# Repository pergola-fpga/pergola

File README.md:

# Pergola FPGA

The Pergola FPGA board is a low-cost, open-source FPGA development board featuring the Lattice ECP5 FPGA.

# Current status

## RevA 0.1

A handful of units have been built for initial test and bringup populated with LFE5U-12F-8BG256C.

It has been tested and works if the fixes below are applied.

### Errata:

- iMX ROM bootloader freezes because the UART RX pin is pulled
   low by the FPGA during boot. (FPGA pin is PL35B_VREF_1_6)
   A 4K7 pull-up is probably not enough, the voltage drops to 2.9V.
   Workaround: Bodge a 1K pull-up between UART_RX and 3V3.
- Wrong load caps for the xtal. Should be 20pF.
- SWD IO and CLK are swapped on the silk.
- IMX_BOOT_MODE_0 and IMX_BOOT_MODE_1 are swapped on the silk.
- A 1K pull-down is on the `~FPGA_HOLD~` net to allow the iMX to use the flash exclusively during boot-up.

# Firmware
TODO.

Currently I have a very ugly test project that can be loaded into the iMX's RAM using the ROM bootloader. This will open up a CDC interface that can be used to send a bitstream to the FPGA.

Currently working on porting the UF2 bootloader in order to update the firmware easily using USB and not having to use the SWD pins.

Current *horrible* hack is located over at [git.xil.se](https://git.xil.se/kbeckmann/pergola_fw) and contains a prebuilt binary.

The firmware will expose a cdc_acm device over USB. To program a bitstream, you simply have to write the number of bytes it is, followed by a newline (`\n`), followed by the bitstream.

# Getting started

- Clone my fork of the imx usb loader project:
```
git clone https://github.com/kbeckmann/imx_usb_loader && cd imx_usb_loader
```
- Checkout the `imxrt1010` branch:
```
git checkout imxrt1010
```
- Build it:
```
make
```
- Clone this repository and change to the firmware directory: (firmware is built from https://git.xil.se/kbeckmann/pergola_fw)
```
cd .. && git clone https://github.com/pergola-fpga/pergola && cd pergola/firmware
```
- Run the loader:
```
../../imx_usb_loader/imx_usb
```
. You might have to run it with `sudo`.
- Check `dmesg` to see if you got a cdc_acm device, e.g. `ttyACM0`
- Now you'll be able to send a bitstream to the board:
```
export ACM_DEVICE=/dev/ttyACM0
export PROGRAM_BIN=path/to/your/top.bin

# If you don't have setup udev rules
sudo chown $UID:$GID $ACM_DEVICE

# Configure the ACM device to be raw, this prevents weird stuff from happening when we send raw binary data.
stty -F $ACM_DEVICE 300 raw -clocal -echo icrnl;
sleep 0.01;
cat $ACM_DEVICE &;
echo -n "$(stat -c%s $PROGRAM_BIN)\n" > $ACM_DEVICE;
cp $PROGRAM_BIN $ACM_DEVICE; sync
```

- This should generate the following output more or less:
```
Reading 582369 bytes
READ_ID: ff ff ff ff 21 11 10 43

Done programming. FPGA_DONE=1
P E R G O L A

<bytes to load><\n>; Load bitstream to FPGA SRAM
```

- There is also an nmigen board definition in gateware/nmigen_wip/pergola.py

# How to contribute

Feel free to submit a PR, create an issue.

Discussion happens on [Gitter](https://gitter.im/pergola-fpga/Lobby) for the time being. You can also ping [@kbeckmann](https://twitter.com/kbeckmann) on Twitter.

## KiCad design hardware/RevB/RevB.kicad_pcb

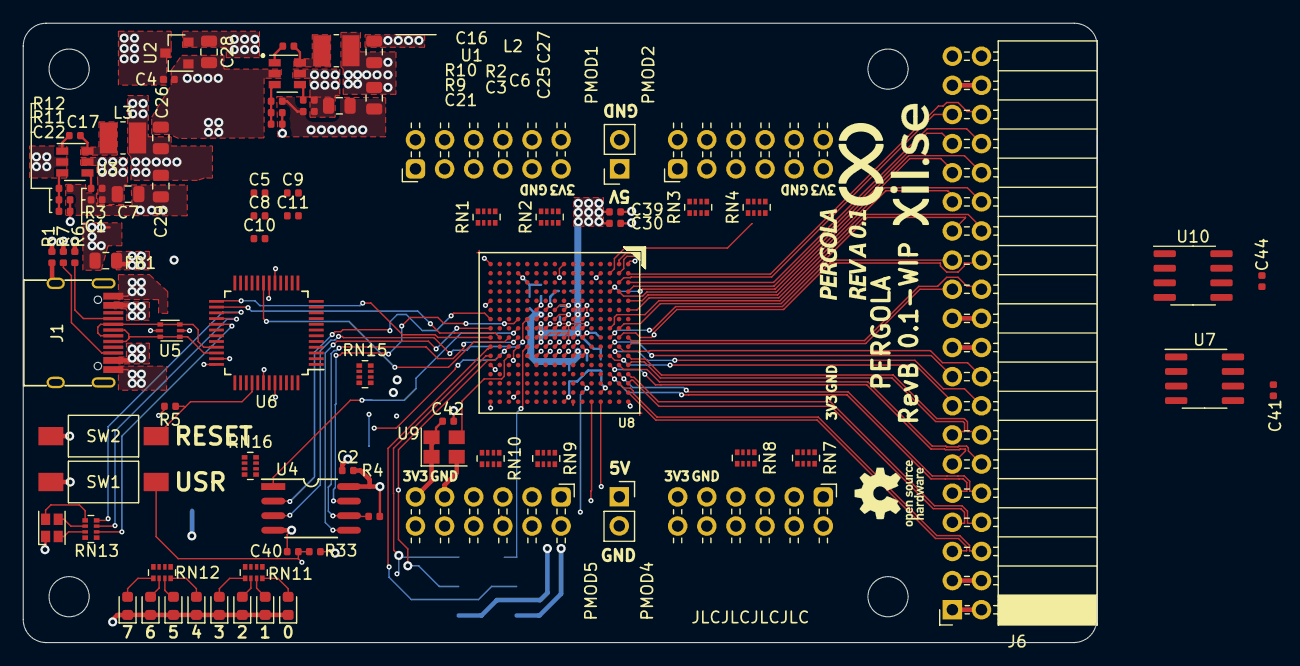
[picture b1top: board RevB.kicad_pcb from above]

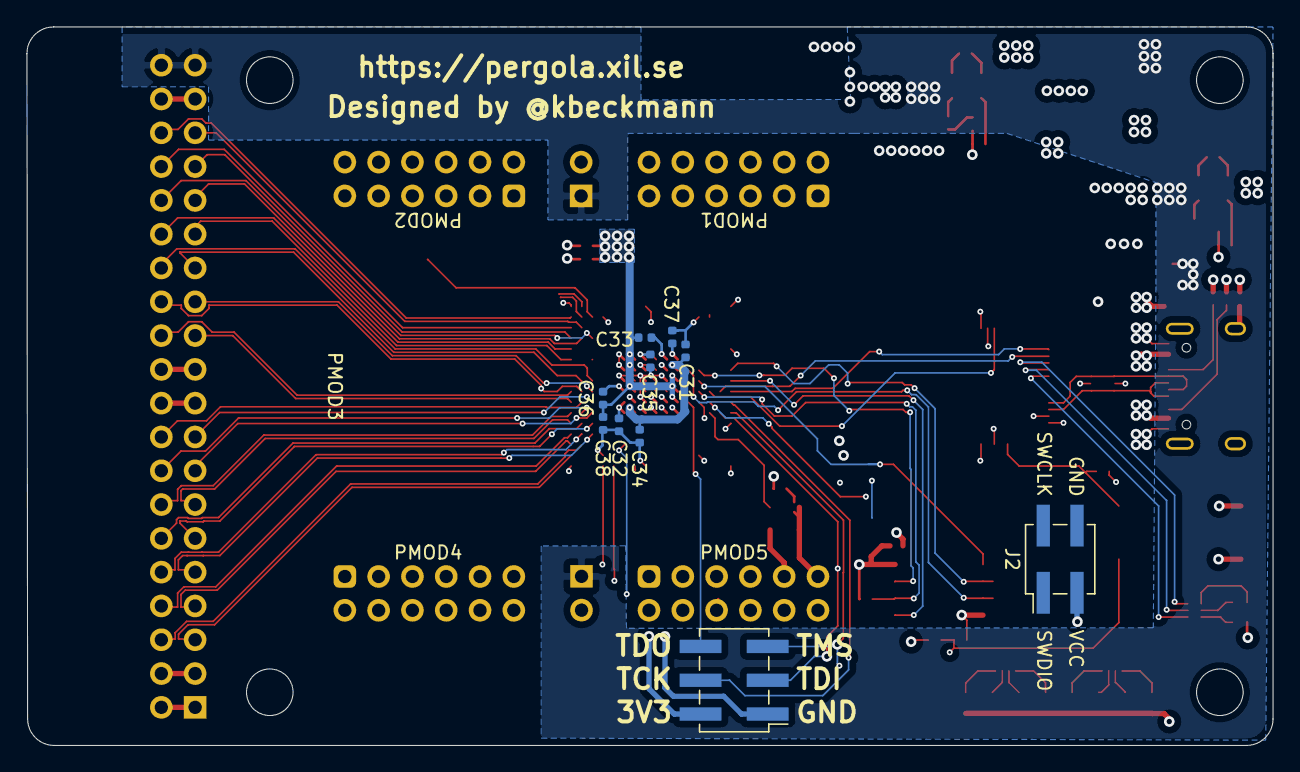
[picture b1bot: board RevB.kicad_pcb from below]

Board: 4 copper layers, 93.7 x 54.0 mm, 100 parts (10 on the bottom side), 147 nets.

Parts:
C1, C2, C3, C5, C8, C9, C10, C11, C16, C17, C30, C31, C32, C33, C34, C35, C36, C37, C38, C39, C40, C41, C42, C44: 100n; C_0402_1005Metric
C4: 4u7; C_0402_1005Metric
C6, C7, C25, C26, C27, C28, C29: 22u; C_0805_2012Metric
C21, C22: 22p; C_0402_1005Metric
D1: LED_ARGB; LED_Cree-PLCC4_2x2mm_CW
D2, D3, D4, D5, D6, D7, D8, D9: LED; LED_0603_1608Metric
FB1: Ferrite_Bead; L_0805_2012Metric
H1, H2, H3, H4: DNP; MountingHole_3.5mm
J1: USB_C_Receptacle_USB2.0; USB_C_Receptacle_GT-USB-7010
J2: DNP Conn_02x02_Odd_Even; PinHeader_2x02_P2.54mm_Vertical_SMD
J3, J5: DNP Conn_01x02; PinSocket_1x02_P2.54mm_Vertical
J4: DNP Conn_02x03_Odd_Even; PinHeader_2x03_P2.54mm_Vertical_SMD
J6: Conn_ULX3S; PinSocket_2x20_P2.54mm_Horizontal
L2, L3: 4u7 1A; L_1008_1210
LOGO1: Logo_Open_Hardware_Small; OSHW-Logo_5.7x6mm_SilkScreen
LOGO2: Logo_Open_Hardware_Small; logo
LOGO3: Logo_Open_Hardware_Small; xil_logo_new
PMOD1, PMOD2, PMOD4, PMOD5: Conn_02x06_Top_Bottom; PMOD_Socket_2x06_P2.54mm_Horizontal
R1: 100k; R_0402_1005Metric
R2, R3, R5, R33: 10k; R_0402_1005Metric
R4: 1k; R_0402_1005Metric
R6, R7: 5k1; R_0402_1005Metric
R9, R11: 15k 1%; R_0402_1005Metric
R10: 18k 1%; R_0402_1005Metric
R12: 3k3 1%; R_0402_1005Metric
RN1, RN2, RN3, RN4, RN7, RN8, RN9, RN10: 22R_x4; R_Array_Convex_4x0402
RN11, RN12, RN13: 2k2_x4; R_Array_Convex_4x0402
RN15, RN16: 10k_x4; R_Array_Convex_4x0402
SW1, SW2: SW_Push; SW_SPST_FSMSM
U1, U3: SY8120B1ABC; SOT-23-6
U2: XC6206P25; SOT-23
U4: SPI Flash W25Q128JVSIQ; SOA008-150-208mil
U5: USBLC6-2P6; SOT-666
U6: ATSAMD21G18A-AUT; TQFP-48_7x7mm_P0.5mm
U7, U10: SPI RAM LY68L6400SLIT; SOIC-8_3.9x4.9mm_P1.27mm
U8: LFE5U-12F-6BG256C; cabga256
U9: 16MHz 20ppm; Crystal_SMD_3225-4Pin_3.2x2.5mm

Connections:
+1V1: C21.2, C25.2, C27.2, C30.2, C33.2, C36.2, C38.2, C39.2, L2.2, R9.2, U8.G6, U8.G7, U8.G9, U8.L8, U8.L9, U8.L10
+2V5: C28.2, C31.2, C34.2, U2.2, U8.G11, U8.L7
+3V3: C2.2, C8.2, C9.2, C10.2, C11.2, C22.2, C26.2, C29.2, C32.2, C35.2, C37.2, C41.2, C42.2, C44.2, D1.1, J2.3, J4.2, J6.1, J6.2, J6.19, J6.20, L3.2, PMOD1.6, PMOD1.12, PMOD2.6, PMOD2.12, PMOD4.6, PMOD4.12, PMOD5.6, PMOD5.12, R4.2, R5.2, R11.2, R33.2, RN15.1, RN15.3, RN16.5, RN16.7, RN16.8, U4.8, U6.6, U6.17, U6.36, U6.44, U7.8, U8.F6, U8.F7, U8.F10, U8.F11, U8.H6, U8.H7, U8.H11, U8.J6, U8.J7, U8.J11, U8.K11, U8.L6, U8.L11, U9.1, U9.4, U10.8
/CLK_16MHZ: U8.P11, U9.3
/FPGA_CFG0: RN15.7, U8.N10
/FPGA_CFG1: RN15.6, U8.P10
/FPGA_CFG2: RN15.5, U8.R10
/FPGA_CONFIG_CLK: R4.1, U4.6, U6.10, U8.N9
/FPGA_DONE: U6.19, U8.P9
/FPGA_SPI_D0: U4.5, U8.T8
/FPGA_SPI_D1: U4.2, U8.T7
/FPGA_SPI_D2: U4.3, U8.M7
/FPGA_SPI_D3: U4.7, U8.N7
/FPGA_~CS_DI: RN15.8, U4.1, U6.9, U8.N8
/FPGA_~INIT: U6.25, U8.T9
/FPGA_~PROGRAM: U6.26, U8.R9
/G0+: J6.6, U8.B14
/G0-: J6.5, U8.A15
/G1+: J6.8, U8.A13
/G1-: J6.7, U8.A14
/G2+: J6.10, U8.B13
/G2-: J6.9, U8.C13
/G3+: J6.12, U8.B12
/G3-: J6.11, U8.C12
/G4+: J6.14, U8.A11
/G4-: J6.13, U8.A12
/G5+: J6.16, U8.B11
/G5-: J6.15, U8.C11
/G6+: J6.18, U8.B10
/G6-: J6.17, U8.C10
/G7+: J6.24, U8.A9
/G7-: J6.23, U8.A10
/G8+: J6.26, U8.B9
/G8-: J6.25, U8.C9
/G9+: J6.28, U8.C8
/G9-: J6.27, U8.B8
/G10+: J6.30, U8.A5
/G10-: J6.29, U8.A6
/G11+: J6.32, U8.C4
/G11-: J6.31, U8.B4
/G12+: J6.34, U8.A3
/G12-: J6.33, U8.A4
/G13+: J6.36, U8.A2
/G13-: J6.35, U8.B3
/JTAG_TCK: J4.4, RN16.3, U6.14, U8.T10
/JTAG_TDI: J4.3, RN16.2, U6.13, U8.R11
/JTAG_TDO: J4.6, RN16.1, U6.15, U8.M10
/JTAG_TMS: J4.5, RN16.4, U6.16, U8.T11
/LED0: RN11.1, U8.F15
/LED1: RN11.2, U8.E16
/LED2: RN11.3, U8.E15
/LED3: RN11.4, U8.D16
/LED4: RN12.1, U8.C16
/LED5: RN12.2, U8.C15
/LED6: RN12.3, U8.B16
/LED7: RN12.4, U8.B15
/LED_B: RN13.6, U6.29
/LED_G: RN13.7, U6.28
/LED_R: RN13.8, U6.27
/MCU_SWCLK: J2.1, U6.45
/MCU_SWDIO: J2.2, U6.46
/MCU_~RESET~: R5.1, SW2.1, U6.40
/PMOD1_1: PMOD1.1, RN1.8
/PMOD1_1x: RN1.1, U8.P2
/PMOD1_2: PMOD1.2, RN1.6
/PMOD1_2x: RN1.3, U8.L1
/PMOD1_3: PMOD1.3, RN2.8
/PMOD1_3x: RN2.1, U8.J2
/PMOD1_4: PMOD1.4, RN2.6
/PMOD1_4x: RN2.3, U8.H2
/PMOD1_5: PMOD1.7, RN1.7
/PMOD1_5x: RN1.2, U8.N1
/PMOD1_6: PMOD1.8, RN1.5
/PMOD1_6x: RN1.4, U8.L2
/PMOD1_7: PMOD1.9, RN2.7
/PMOD1_7x: RN2.2, U8.J1
/PMOD1_8: PMOD1.10, RN2.5
/PMOD1_8x: RN2.4, U8.G1
/PMOD2_1: PMOD2.1, RN3.8
/PMOD2_1x: RN3.1, U8.G2
/PMOD2_2: PMOD2.2, RN3.6
/PMOD2_2x: RN3.3, U8.E2
/PMOD2_3: PMOD2.3, RN4.8
/PMOD2_3x: RN4.1, U8.C1
/PMOD2_4: PMOD2.4, RN4.6
/PMOD2_4x: RN4.3, U8.B1
/PMOD2_5: PMOD2.7, RN3.7
/PMOD2_5x: RN3.2, U8.F1
/PMOD2_6: PMOD2.8, RN3.5
/PMOD2_6x: RN3.4, U8.D1
/PMOD2_7: PMOD2.9, RN4.7
/PMOD2_7x: RN4.2, U8.C2
/PMOD2_8: PMOD2.10, RN4.5
/PMOD2_8x: RN4.4, U8.B2
/PMOD4_1: PMOD4.1, RN7.8
/PMOD4_2: PMOD4.2, RN7.6
/PMOD4_3: PMOD4.3, RN8.8
/PMOD4_4: PMOD4.4, RN8.6
/PMOD4_5: PMOD4.7, RN7.7
/PMOD4_6: PMOD4.8, RN7.5
/PMOD4_7: PMOD4.9, RN8.7
/PMOD4_8: PMOD4.10, RN8.5
/PMOD5_1: PMOD5.1, RN9.8
/PMOD5_1x: RN9.1, U8.F16
/PMOD5_2: PMOD5.2, RN9.6
/PMOD5_2x: RN9.3, U8.G16
/PMOD5_3: PMOD5.3, RN10.8
/PMOD5_3x: RN10.1, U8.J16
/PMOD5_4: PMOD5.4, RN10.6
/PMOD5_4x: RN10.3, U8.L16
/PMOD5_5: PMOD5.7, RN9.7
/PMOD5_5x: RN9.2, U8.G15
/PMOD5_6: PMOD5.8, RN9.5
/PMOD5_6x: RN9.4, U8.H15
/PMOD5_7: PMOD5.9, RN10.7
/PMOD5_7x: RN10.2, U8.J15
/PMOD5_8: PMOD5.10, RN10.5
/PMOD5_8x: RN10.4, U8.L15
/SW_USER: C40.1, R33.1, SW1.1, U8.F14
/USB_DM: J1.A7, J1.B7, U5.3, U5.4, U6.33
/USB_DP: J1.A6, J1.B6, U5.1, U5.6, U6.34
/USB_SHIELD: J1.S1, R1.1
/VBUS_UNFILTERED: FB1.2, J1.A4, J1.A9, J1.B4, J1.B9, U5.5
GND: C1.1, C2.1, C3.1, C4.1, C5.1, C6.1, C7.1, C8.1, C9.1, C10.1, C11.1, C25.1, C26.1, C27.1, C28.1, C29.1, C30.1, C31.1, C32.1, C33.1, C34.1, C35.1, C36.1, C37.1, C38.1, C39.1, C40.2, C41.1, C42.1, C44.1, D2.1, D3.1, D4.1, D5.1, D6.1, D7.1, D8.1, D9.1, J1.A1, J1.A12, J1.B1, J1.B12, J2.4, J3.2, J4.1, J5.2, J6.3, J6.4, J6.21, J6.22, J6.37, J6.38, PMOD1.5, PMOD1.11, PMOD2.5, PMOD2.11, PMOD4.5, PMOD4.11, PMOD5.5, PMOD5.11, R1.2, R6.2, R7.2, R10.1, R12.1, RN15.2, RN15.4, RN16.6, SW1.2, SW2.2, U1.2, U2.1, U3.2, U4.4, U5.2, U6.5, U6.18, U6.35, U6.42, U7.4, U8.A1, U8.A16, U8.D2, U8.D15, U8.F8, U8.F9, U8.G8, U8.G10, U8.H1, U8.H8, U8.H9, U8.H10, U8.H16, U8.J8, U8.J9, U8.J10, U8.K6, U8.K7, U8.K8, U8.K9, U8.K10, U8.N2, U8.N15, U8.T1, U8.T5, U8.T12, U8.T16, U9.2, U10.4
unnamed: C5.2, U6.43
unnamed: C16.1, U1.1
unnamed: C16.2, L2.1, U1.6
unnamed: C17.1, U3.1
unnamed: C17.2, L3.1, U3.6
unnamed: C21.1, R9.1, R10.2, U1.3
unnamed: C22.1, R11.1, R12.2, U3.3
unnamed: D1.2, RN13.1
unnamed: D1.3, RN13.2
unnamed: D1.4, RN13.3
unnamed: D2.2, RN11.8
unnamed: D3.2, RN11.7
unnamed: D4.2, RN11.6
unnamed: D5.2, RN11.5
unnamed: D6.2, RN12.8
unnamed: D7.2, RN12.7
unnamed: D8.2, RN12.6
unnamed: D9.2, RN12.5
unnamed: J1.A5, R6.1
unnamed: J1.B5, R7.1
unnamed: R2.2, U1.4
unnamed: R3.2, U3.4
VBUS: C1.2, C3.2, C4.2, C6.2, C7.2, FB1.1, J3.1, J5.1, J6.39, J6.40, R2.1, R3.1, U1.5, U2.3, U3.5

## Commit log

2019-11-17 Pergola RevA 0.1
2019-12-01 Add errata/todo
2019-12-01 Update errata/todo
2019-12-01 Changed xtal load caps to 20pF
2019-12-08 RevA 0.2 updates
2019-12-09 Fix errata, swd io/clk are swapped on the silk
2019-12-20 Vendor footprints/symbols
2019-12-20 Add README.md
2019-12-20 Rename gerber directory
2019-12-21 hardware: Add USB TH pads solderpaste layer
    This was not being done before, leading to
    stencils missing the through-hole pads for
    the USB connector.
2019-12-21 hardware: Fix silkscreen for bootmode and swd
    - SWD IO and CLK were swapped on the silk.
    - IMX_BOOT_MODE_0 and IMX_BOOT_MODE_1 were swapped on the silk.
2019-12-27 Update readme and add prebuilt firmware
2019-12-28 Add nmigen board wip
2020-04-19 Add note about SW_USR
2020-04-26 Add pinout markdown file
2020-08-23 RevB initial commit
2020-08-23 Fix weird via
2020-08-23 progress
2020-08-24 Update BOM
2020-08-25 Routing WIP experiment
